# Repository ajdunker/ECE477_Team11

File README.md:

# ECE 477 Team 11
ECE 477 Team 11 - Beer Me

Team Members:

Dan Suciu - Team Captain  
Mitch Bouma  
Alex Dunker  
Nadav Zinger  

Additional documentation available on our team website: https://engineering.purdue.edu/477grp11/

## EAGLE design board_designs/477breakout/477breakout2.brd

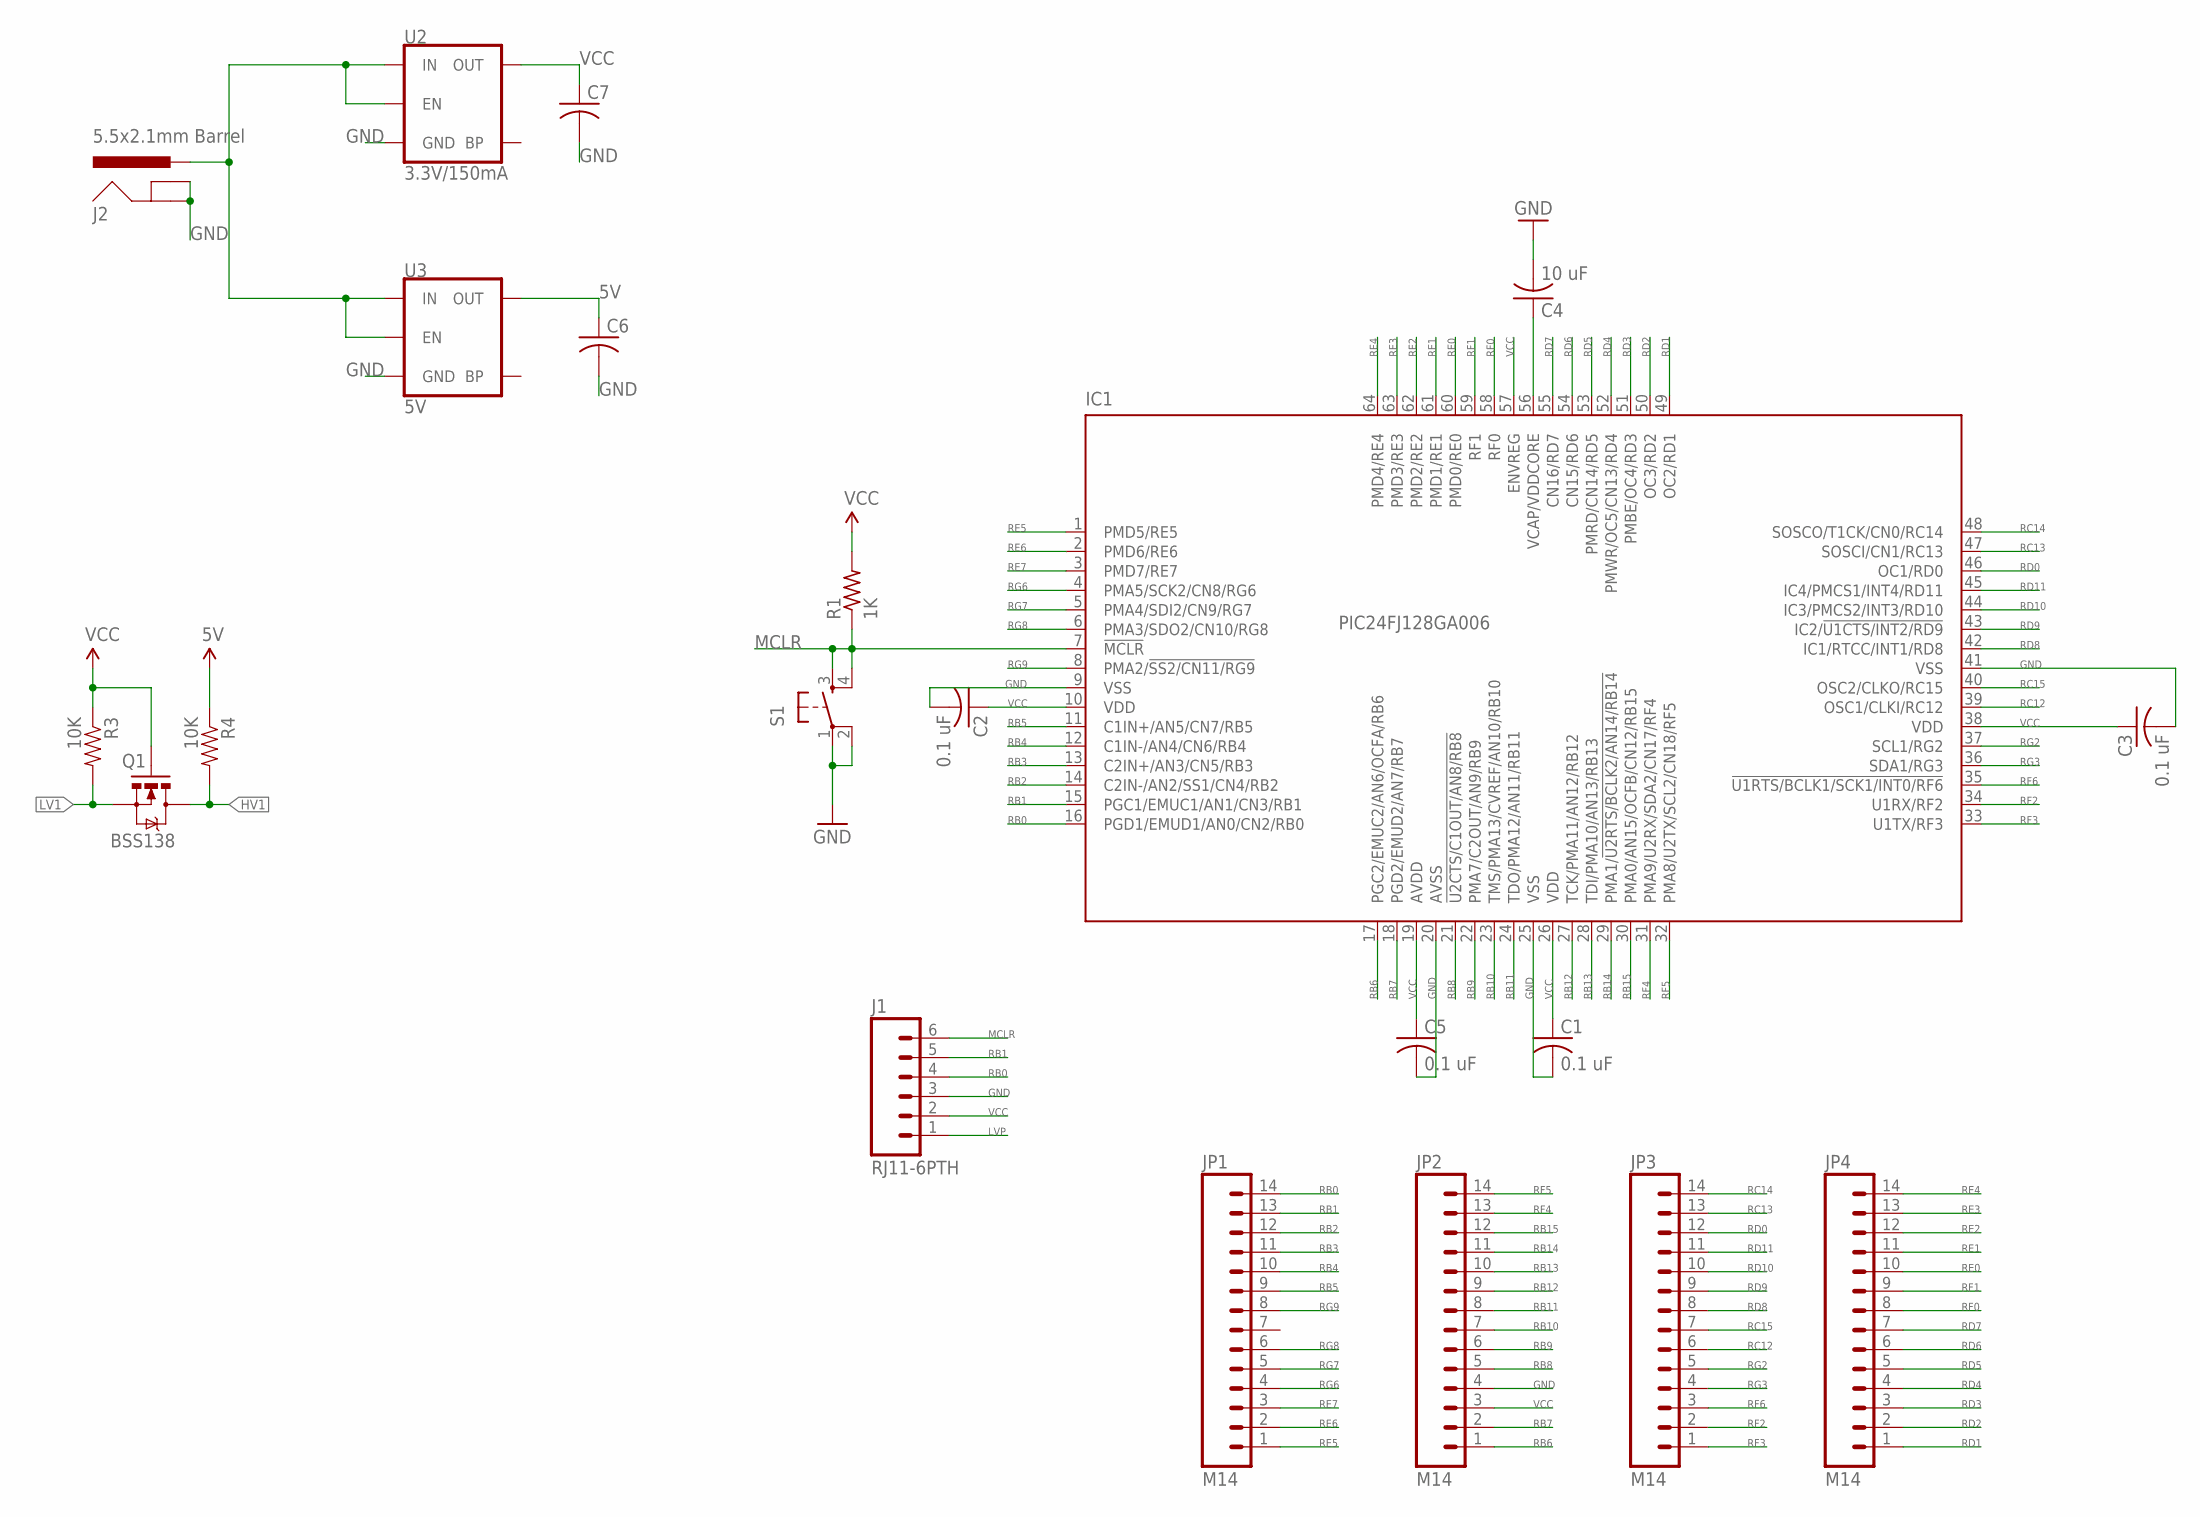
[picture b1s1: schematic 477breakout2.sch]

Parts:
C1, C2, C3, C5: 0.1 uF; C0402
C4: 10 uF; C0805
C6, C7: C-USC1206; C1206
IC1: PIC24FJ128GA006; TQFP64-10X10
J1: RJ11-6PTH; RJ11-6
J2: 5.5x2.1mm Barrel; POWER_JACK_SMD
JP1, JP2, JP3, JP4: M14; 1X14
Q1: BSS138; SOT23-3
R1: 1K; 0204/7
R3, R4: 10K; 0603-RES
S1: TAC_SWITCHPTH; TACTILE-PTH
U2: 3.3V/150mA; SOT23-5
U3: 5V; SOT23-5

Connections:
5V: C6.1, R4.1, U3.5 (OUT)
GND: C1.2, C2.2, C3.2, C4.2, C5.2, C6.2, C7.2, IC1.9 (VSS), IC1.20 (AVSS), IC1.25 (VSS), IC1.41 (VSS), J1.3, J2.GND (GNDBREAK), J2.P$4 (GND), JP2.4, S1.1, S1.2, U2.2 (GND), U3.2 (GND)
HV1: Q1.3 (D), R4.2
LV1: Q1.2 (S), R3.2
LVP: J1.1
MCLR: IC1.7 (!MCLR), J1.6, R1.1, S1.3, S1.4
unnamed: C4.1, IC1.56 (VCAP/VDDCORE)
unnamed: J2.VIN0 (PWR), U2.1 (IN), U2.3 (EN), U3.1 (IN), U3.3 (EN)
RB0: IC1.16 (PGD1/EMUD1/AN0/CN2/RB0), J1.4, JP1.14
RB1: IC1.15 (PGC1/EMUC1/AN1/CN3/RB1), J1.5, JP1.13
RB2: IC1.14 (C2IN-/AN2/SS1/CN4/RB2), JP1.12
RB3: IC1.13 (C2IN+/AN3/CN5/RB3), JP1.11
RB4: IC1.12 (C1IN-/AN4/CN6/RB4), JP1.10
RB5: IC1.11 (C1IN+/AN5/CN7/RB5), JP1.9
RB6: IC1.17 (PGC2/EMUC2/AN6/OCFA/RB6), JP2.1
RB7: IC1.18 (PGD2/EMUD2/AN7/RB7), JP2.2
RB8: IC1.21 (!U2CTS/C1OUT/AN8/RB8), JP2.5
RB9: IC1.22 (PMA7/C2OUT/AN9/RB9), JP2.6
RB10: IC1.23 (TMS/PMA13/CVREF/AN10/RB10), JP2.7
RB11: IC1.24 (TDO/PMA12/AN11/RB11), JP2.8
RB12: IC1.27 (TCK/PMA11/AN12/RB12), JP2.9
RB13: IC1.28 (TDI/PMA10/AN13/RB13), JP2.10
RB14: IC1.29 (PMA1/!U2RTS/BCLK2/AN14/RB14), JP2.11
RB15: IC1.30 (PMA0/AN15/OCFB/CN12/RB15), JP2.12
RC12: IC1.39 (OSC1/CLKI/RC12), JP3.6
RC13: IC1.47 (SOSCI/CN1/RC13), JP3.13
RC14: IC1.48 (SOSCO/T1CK/CN0/RC14), JP3.14
RC15: IC1.40 (OSC2/CLKO/RC15), JP3.7
RD0: IC1.46 (OC1/RD0), JP3.12
RD1: IC1.49 (OC2/RD1), JP4.1
RD2: IC1.50 (OC3/RD2), JP4.2
RD3: IC1.51 (PMBE/OC4/RD3), JP4.3
RD4: IC1.52 (PMWR/OC5/CN13/RD4), JP4.4
RD5: IC1.53 (PMRD/CN14/RD5), JP4.5
RD6: IC1.54 (CN15/RD6), JP4.6
RD7: IC1.55 (CN16/RD7), JP4.7
RD8: IC1.42 (IC1/RTCC/INT1/RD8), JP3.8
RD9: IC1.43 (IC2/!U1CTS/INT2/RD9), JP3.9
RD10: IC1.44 (IC3/PMCS2/INT3/RD10), JP3.10
RD11: IC1.45 (IC4/PMCS1/INT4/RD11), JP3.11
RE0: IC1.60 (PMD0/RE0), JP4.10
RE1: IC1.61 (PMD1/RE1), JP4.11
RE2: IC1.62 (PMD2/RE2), JP4.12
RE3: IC1.63 (PMD3/RE3), JP4.13
RE4: IC1.64 (PMD4/RE4), JP4.14
RE5: IC1.1 (PMD5/RE5), JP1.1
RE6: IC1.2 (PMD6/RE6), JP1.2
RE7: IC1.3 (PMD7/RE7), JP1.3
RF0: IC1.58 (RF0), JP4.8
RF1: IC1.59 (RF1), JP4.9
RF2: IC1.34 (U1RX/RF2), JP3.2
RF3: IC1.33 (U1TX/RF3), JP3.1
RF4: IC1.31 (PMA9/U2RX/SDA2/CN17/RF4), JP2.13
RF5: IC1.32 (PMA8/U2TX/SCL2/CN18/RF5), JP2.14
RF6: IC1.35 (!U1RTS/BCLK1/SCK1/INT0/RF6), JP3.3
RG2: IC1.37 (SCL1/RG2), JP3.5
RG3: IC1.36 (SDA1/RG3), JP3.4
RG6: IC1.4 (PMA5/SCK2/CN8/RG6), JP1.4
RG7: IC1.5 (PMA4/SDI2/CN9/RG7), JP1.5
RG8: IC1.6 (PMA3/SDO2/CN10/RG8), JP1.6
RG9: IC1.8 (PMA2/!SS2/CN11/RG9), JP1.8
VCC: C1.1, C2.1, C3.1, C5.1, C7.1, IC1.10 (VDD), IC1.19 (AVDD), IC1.26 (VDD), IC1.38 (VDD), IC1.57 (ENVREG), J1.2, JP2.3, Q1.1 (G), R1.2, R3.1, U2.5 (OUT)

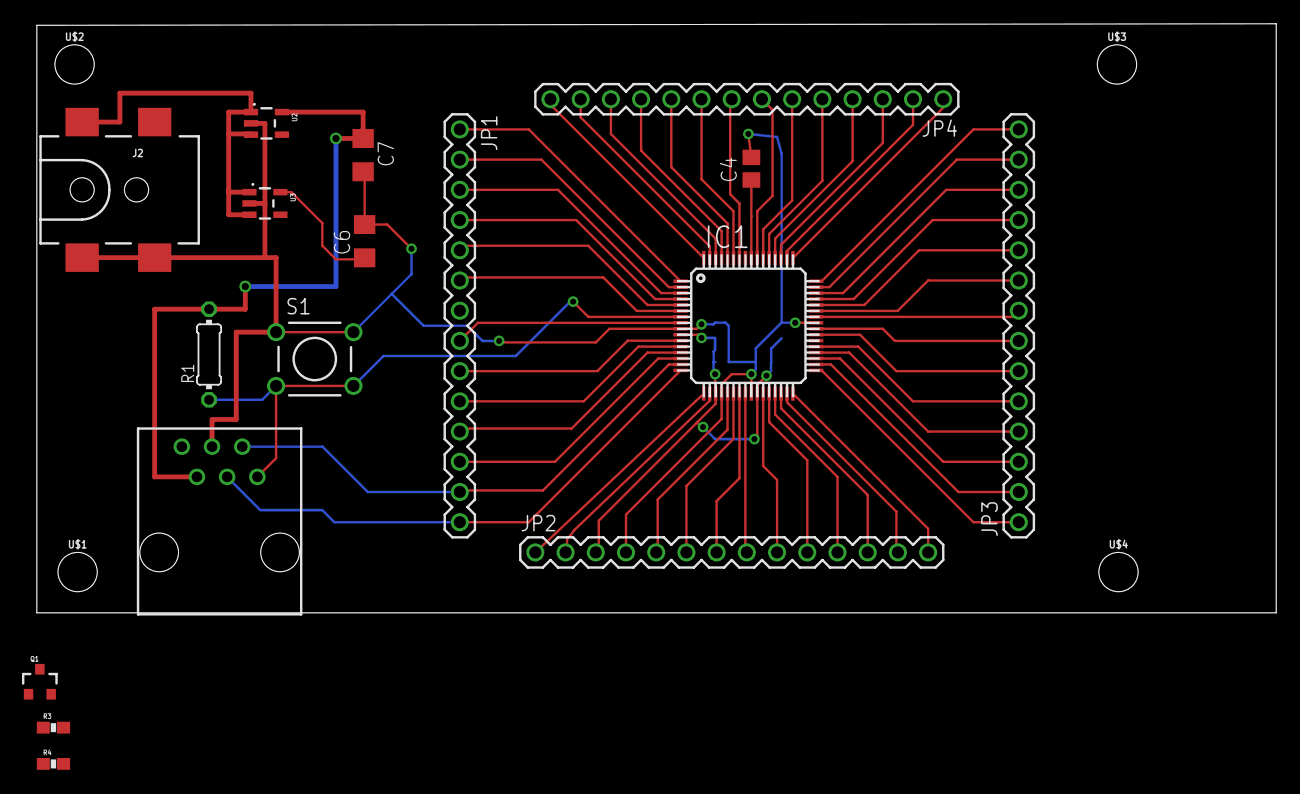
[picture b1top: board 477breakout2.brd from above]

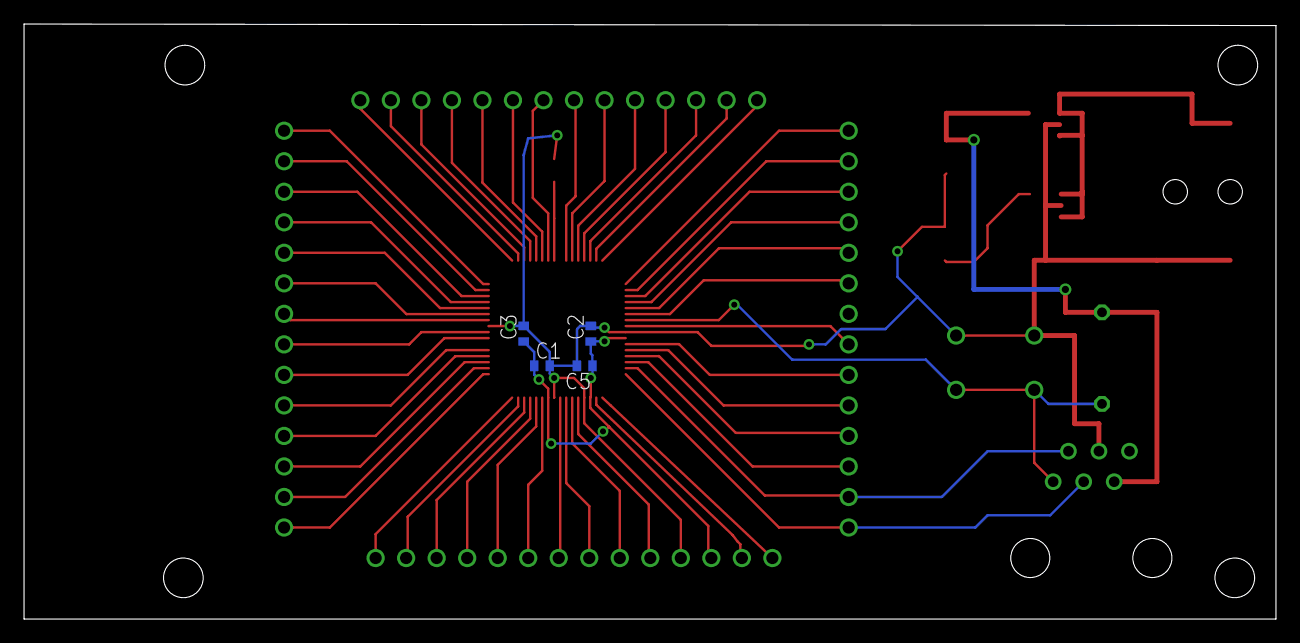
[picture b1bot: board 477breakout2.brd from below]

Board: 2 copper layers, 104.2 x 49.5 mm, 25 parts (4 on the bottom side), 61 nets.

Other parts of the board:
U$1, U$2, U$3, U$4: STAND-OFF

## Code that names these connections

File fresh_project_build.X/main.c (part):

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#define LAUNCH 5

// limit switch "button style" port declarations
#define beer_PORT PORTDbits.RD11
#define beer_TRIS TRISDbits.TRISD11
/*
// LED 1
#define led1_PORT PORTEbits.RE0
#define led1_TRIS TRISEbits.TRISE0
// LED 2
#define led2_PORT PORTEbits.RE1
#define led2_TRIS TRISEbits.TRISE1
// LED 3
#define led3_PORT PORTEbits.RE2
#define led3_TRIS TRISEbits.TRISE2
// LED 4
#define led4_PORT PORTFbits.RF1
#define led4_TRIS TRISFbits.TRISF1
// LED 5
#define led5_PORT PORTEbits.RE4
#define led5_TRIS TRISEbits.TRISE4
 */
// h bridge enable
#define hb_enable_PORT PORTDbits.RD1
#define hb_enable_TRIS TRISDbits.TRISD1
// h bridge port 1
#define hb1_PORT PORTDbits.RD2
#define hb1_TRIS TRISDbits.TRISD2
// h bridge port 2
#define hb2_PORT PORTFbits.RF0
#define hb2_TRIS TRISFbits.TRISF0
// solenoid
#define solenoid_PORT PORTEbits.RE4
#define solenoid_TRIS TRISEbits.TRISE4
// pump
#define pump_PORT PORTEbits.RE3
#define pump_TRIS TRISEbits.TRISE3

// *****************************************************************************
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
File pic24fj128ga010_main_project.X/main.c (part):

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#define LAUNCH_PREP 4
#define LAUNCH 5
// PWM port declarations
#define PWM_PORT1  PORTDbits.RD1
#define PWM_TRIS1  TRISDbits.TRISD1
// limit switch "button style" port declarations
#define limit_PORT PORTDbits.RD11
#define limit_TRIS  TRISDbits.TRISD11
//#define beer_PORT PORTDbits.RD11
//#define beer_TRIS TRISDbits.TRISD11
// UART ports
#define RX_port PORTFbits.RF2
#define RX_TRIS TRISFbits.TRISF2
#define CTS_port PORTDbits.RD9
#define CTS_TRIS TRISDbits.TRISD9

// *****************************************************************************
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
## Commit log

2017-01-11 Added Course Documents
    Added a number of the course documents to the github.
2017-01-11 Organization
2017-02-01 Added board design and sync scripts
2017-02-01 Ignore changes
2017-02-15 477 Stamp Board
    Added stamp board files.
2017-02-15 Add .gitignore and .gitattributes.
2017-02-15 Add project files.
2017-02-15 Board Changes
2017-02-15 adding micro project files
2017-02-24 added speech recognition
2017-03-03 Updated board designs
2017-03-27 added function for angle calculation/transfer
2017-04-26 test
2017-04-27 finished!!!
2017-04-27 Working code
2017-04-27 Finished Code
    Dan doesn't do commits, so this is the working code for the
    microcontroller.
2017-04-27 Kinect Solution Publish
    Published version for standalone running
2017-04-27 trying exe file
2017-04-27 Board Update
    board
2017-05-02 finished the project! everything now works

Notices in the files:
fresh_project_build.X/main.c:
Copyright (c) 2013 released Microchip Technology Inc.  All rights reserved.
parts and their libraries:
SparkFun-IC-Power: Licensing: Creative Commons ShareAlike 4.0 International - https://creativecommons.org/licenses/by-sa/4.0
